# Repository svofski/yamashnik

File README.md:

yamashnik
=========
Yamaha YIS-503/IIIR MSX-2 MSX-Link hardware and software

This package facilitates use of a remote MSX-2 workstation equipped with network 
module. The only known instance of such workstation is Yamaha YIS-503/IIIR that used
to be deployed in Russian schools in the 1980s.

To operate, a hardware adapter is needed for the PC. It's a USB to Serial converter
with optocouplers needed to connect to MSX workstations. KiCad schematics and PCB
layout are provided.

The host software supports 3 different modes:

1. CP/M upload: files can be uploaded to the RAM disk of builtin CP/M into remote machine
2. BASIC send: BASIC and ROM files can be transferred over network to remote machines
3. A special version of MSX-DOS can be deployed to the remote machine. Its transfers file system requests to the host machine, which then becomes a file server. Disk based MSX-DOS software can be used using this mode. MSX-DOS files MSXDOS.SYS and COMMAND.COM are not included in this package.

#### Compatibility list
- Turbo Pascal 3.0
- Zork

PACKAGE CONTENTS
----------------
- `kicad/` USB to MSXNET adapter [schematic](kicad/yamashnik.pdf) + PCB layout for home making
- `sw/spyvspy/` software that emulates server software and supports various boot protocols

HOW TO BUILD
------------

### MSX-Link Hardware
If you need help, ask someone else to do it for you. There are RS-232 based variants of the adapter too. All through-hole version [here](https://sensi.org/~tnt23/msx) and a breadboard version [here](https://web.archive.org/web/20080620084238/http://msxlink.chat.ru/).

### Software
You need Linux or Darwin/OSX and a sane build environment. `wget` utility is needed to fetch z80asm from savannah. 

It should work in Windows with some POSIX-emulation layer but it's not proven. 

  1. check out or download the source
  2. cd yamashnik/sw
  3. type make
  4. if all is well, msxnet and remote bootstrap files are in yamashnik/sw/spyvspy/build subdirectory

HOW TO USE
----------
[ ] todo

LICENSE
-------
This package is distributed as is. You can do whatever you want with it as long as you give credit to the authors.

- Viacheslav Slavinsky https://caglrc.cc
- Based on research and software by Tim Tashpulatov http://sensi.org/~tnt23/msx

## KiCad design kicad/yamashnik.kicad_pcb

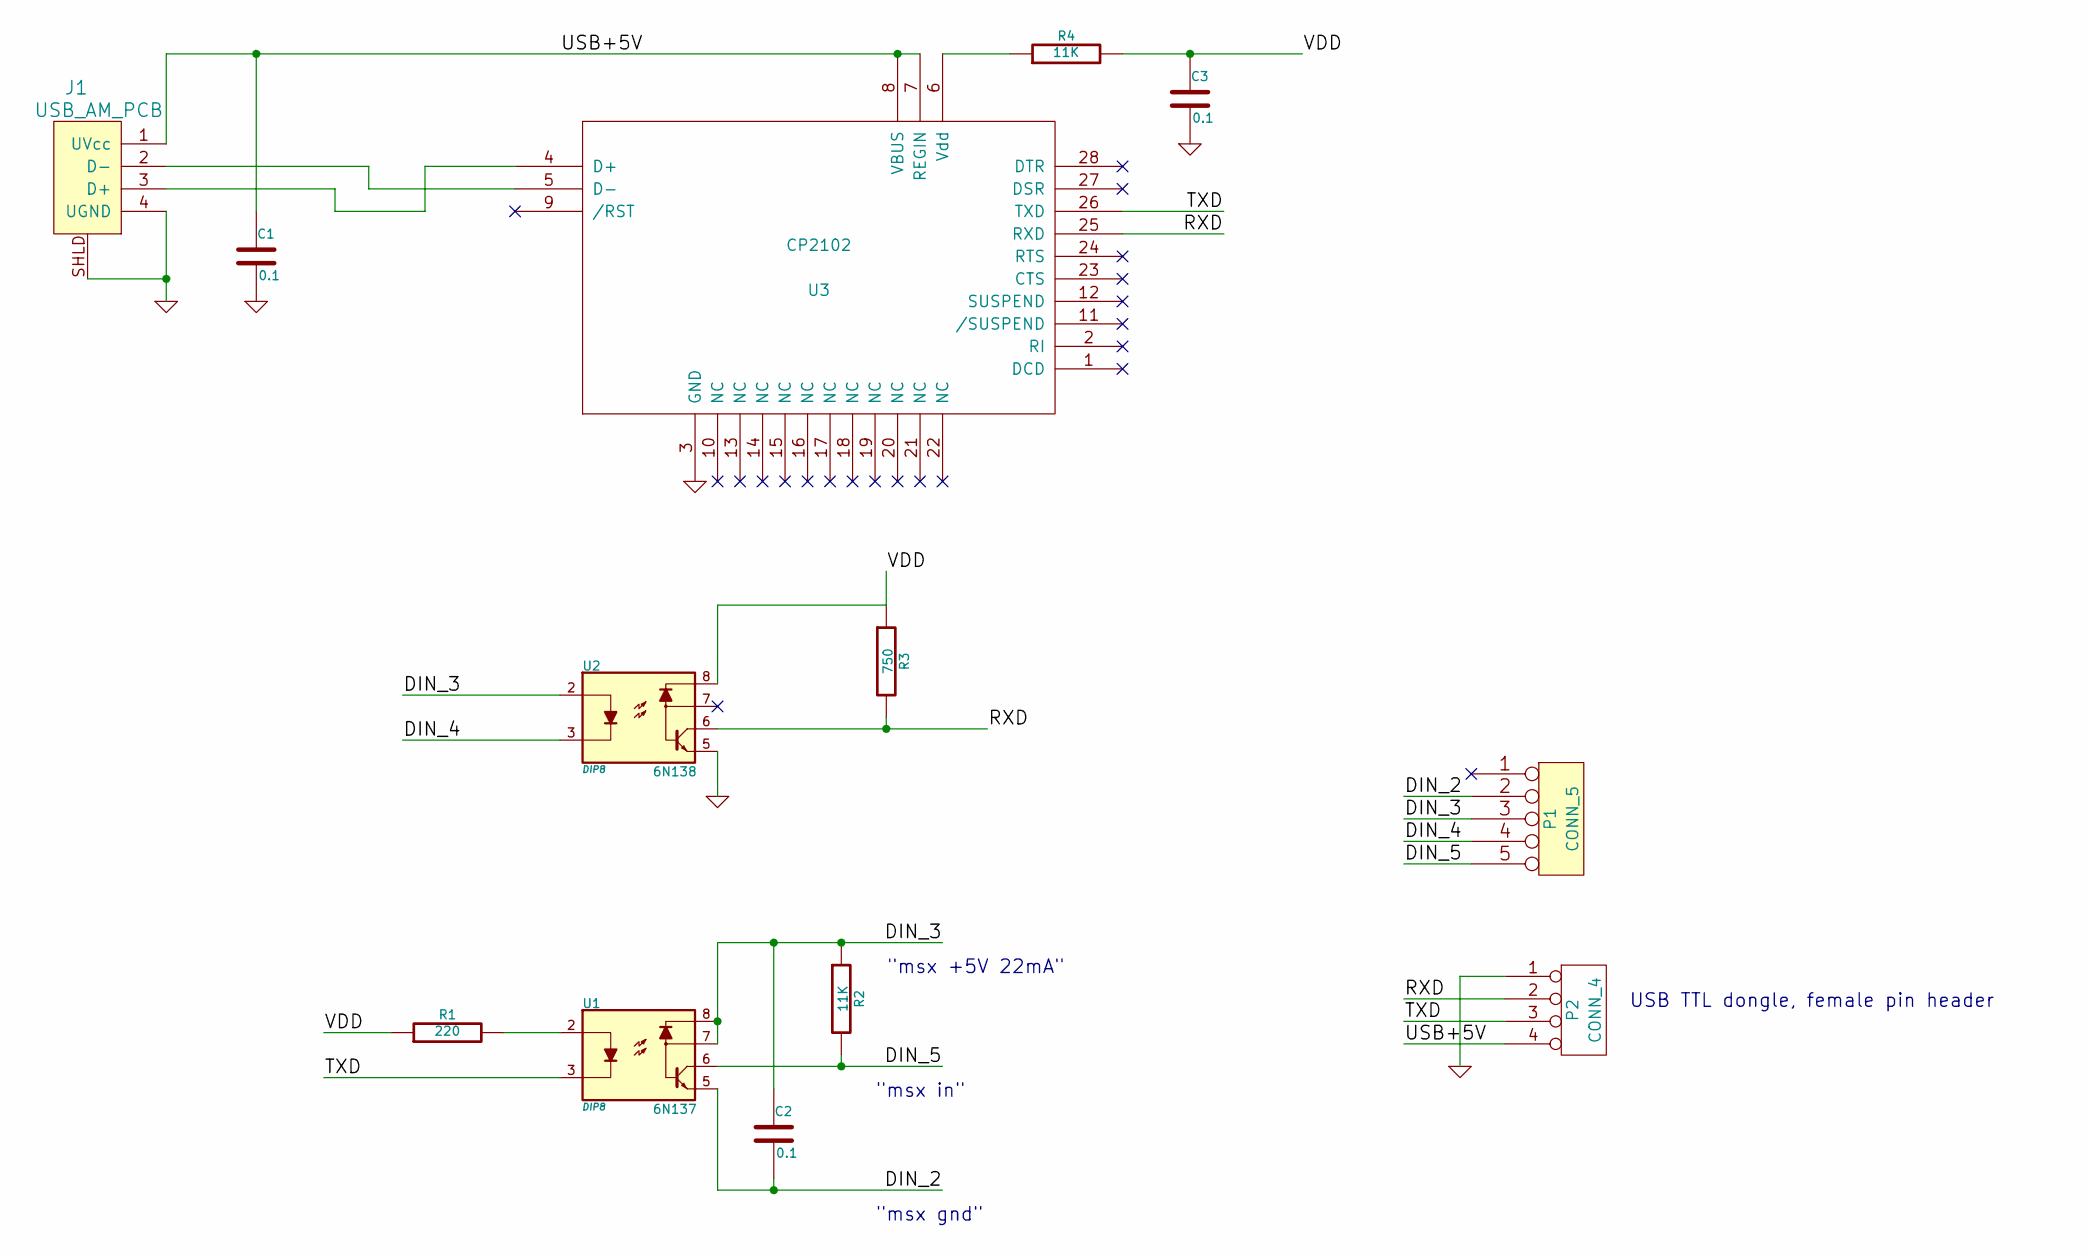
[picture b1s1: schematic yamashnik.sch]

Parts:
C1, C2, C3: 0.1
J1: USB_AM_PCB
P1: CONN_5
P2: CONN_4
R1: 220
R2, R4: 11K
R3: 750
U1: 6N137; DIP8
U2: 6N138; DIP8
U3: CP2102

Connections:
/DIN_2: C2.2, P1.2, U1.5
/DIN_3: C2.1, P1.3, R2.1, U1.7, U1.8, U2.2
/DIN_4: P1.4, U2.3
/DIN_5: P1.5, R2.2, U1.6
/RXD: P2.2, R3.2, U2.6, U3.25 (RXD)
/TXD: P2.3, U1.3, U3.26 (TXD)
/USB+5V: C1.1, J1.1 (UVcc), P2.4, U3.7 (REGIN), U3.8 (VBUS)
/VDD: C3.1, R1.1, R3.1, R4.2, U2.8
GND: C1.2, C3.2, J1.4 (UGND), J1.SHLD, P2.1, U2.5, U3.3 (GND)
unnamed: J1.3 (D+), U3.4 (D+)
unnamed: R4.1, U3.6 (Vdd)
unnamed: J1.2 (D-), U3.5 (D-)
unnamed: R1.2, U1.2

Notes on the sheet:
"msx in"
"msx gnd"
"msx +5V 22mA"
USB TTL dongle, female pin header

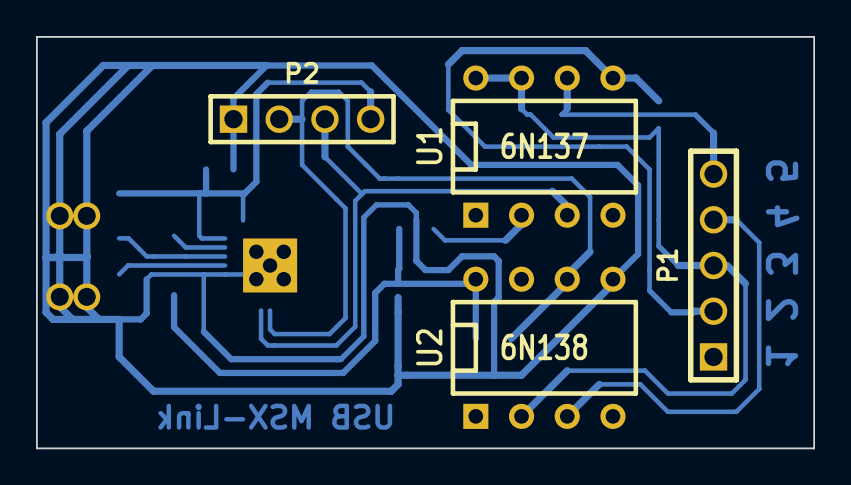
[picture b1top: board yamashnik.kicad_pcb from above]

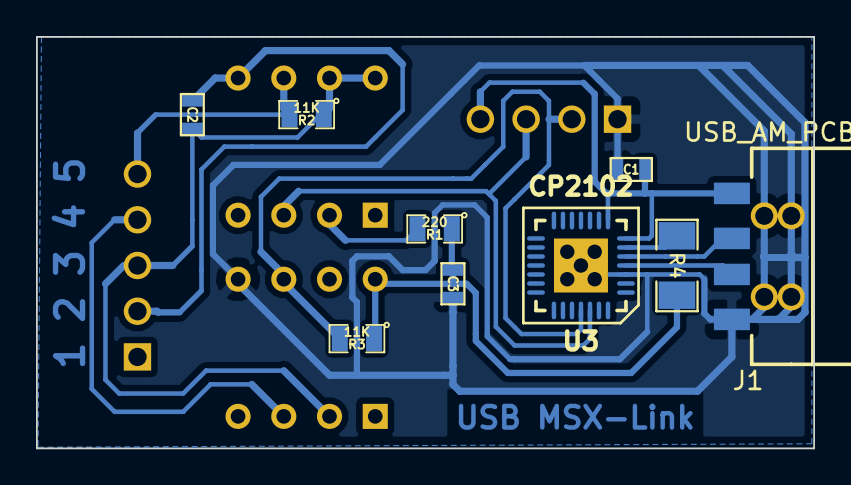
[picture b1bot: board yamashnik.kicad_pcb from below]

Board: 2 copper layers, 43.2 x 22.9 mm, 13 parts (9 on the bottom side), 13 nets.

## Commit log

2014-05-27 brutal migration from https://code.google.com/p/svofski/
2014-05-27 missing basicsend.*
2014-05-27 +Makefile that fetches z80asm from savannah
2014-05-27 gitignore
2014-05-27 build everything into build subdirectory
2014-05-27 formatting weirdness and comments in asm sources
2014-05-27 ignore build/*
2014-05-27 select error in serial, FCB in Func17_RenameFiles
    - ignore several select() errors before termination, they appear to be
    able to happen
    - fix FCB size in spy_bdos_e900.asm Func17_RenameFile
    - add pace constants
2014-05-27 indents in asm
2014-05-28 CAPS toggler clarification
2014-05-29 sped up remote requests
    select timeout is 0.1s now
    reduced pace in SendByte, but it is still necessary
2014-05-31 fixes in serial protocol
    - fixed retrieval of tokens from in put buffer (probably needs a
    complete refactoring, the current scheme is weird)
    - this enabled complete removal of delays between bytes and words on
    the msx side
    - added createFile, renameFile, deleteFile functions
    - stubs for sequentialWrite and absSectorRead (probably the latter is
2014-05-31 implemented sequentialWrite and prettier logging
    - sequential write works, so files can be saved from Turbo Pascal, also
    Zork save games
    - logging at base level prints messages on the same line for repetitive
    operations like read/write
2014-05-31 implemented random write
    turbo pascal can compile to com files now
2014-05-31 #1 crash if no port is specified in --serve
2014-05-31 #3 cp/m ncopy seems to be uploading junk
    - separated dosname into Util class
    - tests for dosname
    - variable expectation time in Serial::waitRx()
    - smoother bubbles in basic send and copy
2014-05-31 update schematic, added pdf drawing
2014-06-01 #8 BDOS 08h doesn't wait for keyboard input
2014-06-01 #9 correct date/time in directory entries
    - also send believable DPB on Get Allocation Information — this still
    ugly and does not fix XDIR
    - added DMA2 (REQ_DMA2) to SpyResponse to enable sending 2 chunks in
    one response
2014-06-01 #9 WARMBOOT implementation
    - implemented warm boot from msxdos.sys that calculates command.com
    checksum and loads it if necessary
    - this changes bootstrap procedure: it now ends with rst 0
    - programs can now return to shell and it appears to be reloading well
    - but death after first command still happens: the prompt appears, but
    the first key press tends to kill cause warmboot, or kill it to death —
2014-06-02 #4 #5 cannot exit MSX-DOS programs
    - can exit
    - added CP/M function 1F because Turbo Pascal _suddenly_ needs it to
    display directory
    - getAllocInfo() removed completely from the server side, client side
    stub just feeds default values
    - in Func15_SequentialWrite removed delay, it probably was useful with
2014-06-03 #10 detect when usb thingy is unplugged and die
2015-09-03 gerber files
2015-09-04 recovered kicad_pcb, updated edge cuts
2023-08-01 build on linux, fixes #11
    not tested, just builds
2024-02-27 Update README.md
    updated breadboard link to web.archive.org
